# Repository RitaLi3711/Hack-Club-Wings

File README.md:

# Hack-Club-Wings
A passion project for making articulated wings. This is for the frame work. the feathers and decorations will be added afterwords.

Journal Entries 

Inspiration + Frame Decision (Dec 6)

I've always wanted to make a cosplay with wings, as it's a common character trait.
However, the key is that these wings will be articulated. Thus, they'll have to move.

Initially, I wanted to decide whether the wings should have feathers or be like bat wings.
It seems that feathers are more common and the folding will be easier as its individual wings.

Moreover, this is the planning stage as I search for information.

The wings will have to fold.
The way they fold is what differs (point of movement).
From past cosplays, there are 2 main frame types.

3 joints
https://youtu.be/Llf2Xc1FtOM?si=F14uOp8mgtAz-DmK
https://youtu.be/ioxxIeyw33Q?si=4gpekAnZgTFiVE0G

1 joint
https://youtu.be/-S2A7ioRvzg?si=h_PVrSaw3obiIKA0
https://youtube.com/shorts/ro5Fy8bAvns?si=yLVc0ShqFhmZ_Usy
For this project, I will be making wings that move at 1 joint, as that is simpler to build.

Change of Plans (Dec 6)
If I decided to do the 1-point plan, I would need to use at least 2 linear actuators.
I could not find this type of motor option on KaiCad + it is quite pricey (amazon $191 for 1)

Many individuals have done the 3-point method, but mechanically by pulling a piece of string.
To incorporate more circuits into this design, I will be connecting a motor to the pulley. Thus, I can also control when the wings go up and down by controlling how much string the pulley pulls(front, back).
20251206_223540

edit*** wait if the mobile part must be the same for both wings...can't I just use 1 linear actuator?

Created Schematic + Wired the PCB (Dec 6-7)
Ok, so turns out I can't just connect the linear actuator directly to the battery. :(

I'll also be using a fuse, motor controller and microcontroller.
I hope that the fuse and controller will prevent me from catching on fire through overheating. After I add all the feathers and cloth, it'd be a fire hazard, especially under a heavy cosplay costume.

The linear actuator has a DC motor built into it already, so I'll be representing it as a regular DC motor on both the schematic and PCB.
The PCB said that there are 0 errors, so hopefully that's a good sign....

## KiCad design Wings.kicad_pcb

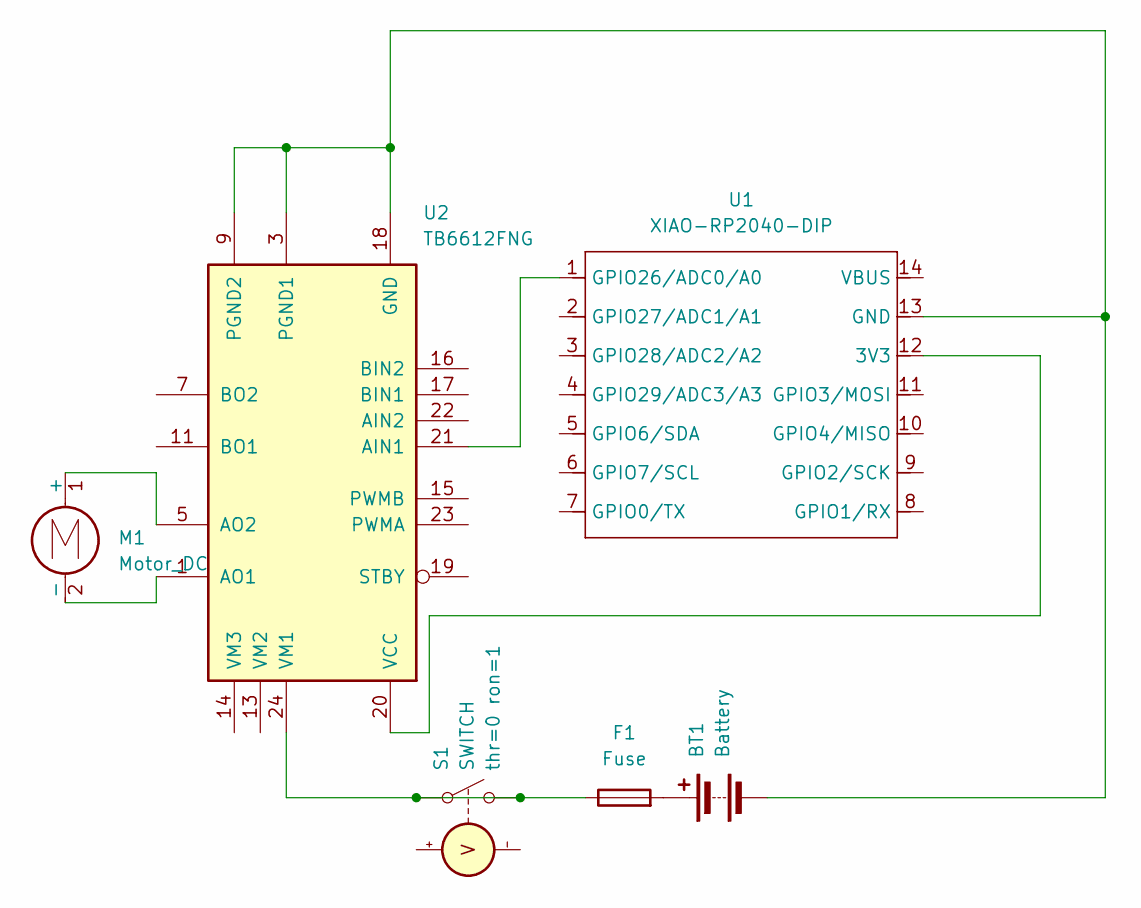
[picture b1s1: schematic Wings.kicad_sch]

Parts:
BT1: Battery; BatteryHolder_Keystone_2479_3xAAA
F1: Fuse; Fuse_1206_3216Metric
M1: Motor_DC; Vybronics_VZ30C1T8219732L
S1: SWITCH; Nidec_Copal_CAS-120A
U1: XIAO-RP2040-DIP
U2: TB6612FNG; SSOP-24_5.3x8.2mm_P0.65mm

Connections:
unnamed: BT1.1 (+), F1.2
unnamed: BT1.2 (-), U1.13 (GND), U2.3 (PGND1), U2.4 (PGND1), U2.9 (PGND2), U2.10 (PGND2), U2.18 (GND)
unnamed: M1.1 (+), U2.5 (AO2), U2.6 (AO2)
unnamed: M1.2 (-), U2.1 (AO1), U2.2 (AO1)
unnamed: F1.1, S1.1 (N+), S1.2 (N-), U2.24 (VM1)
unnamed: U1.12 (3V3), U2.20 (VCC)
unnamed: U1.1 (GPIO26/ADC0/A0), U2.21 (AIN1)
unnamed: U2.11 (BO1), U2.12 (BO1)
unnamed: U2.7 (BO2), U2.8 (BO2)

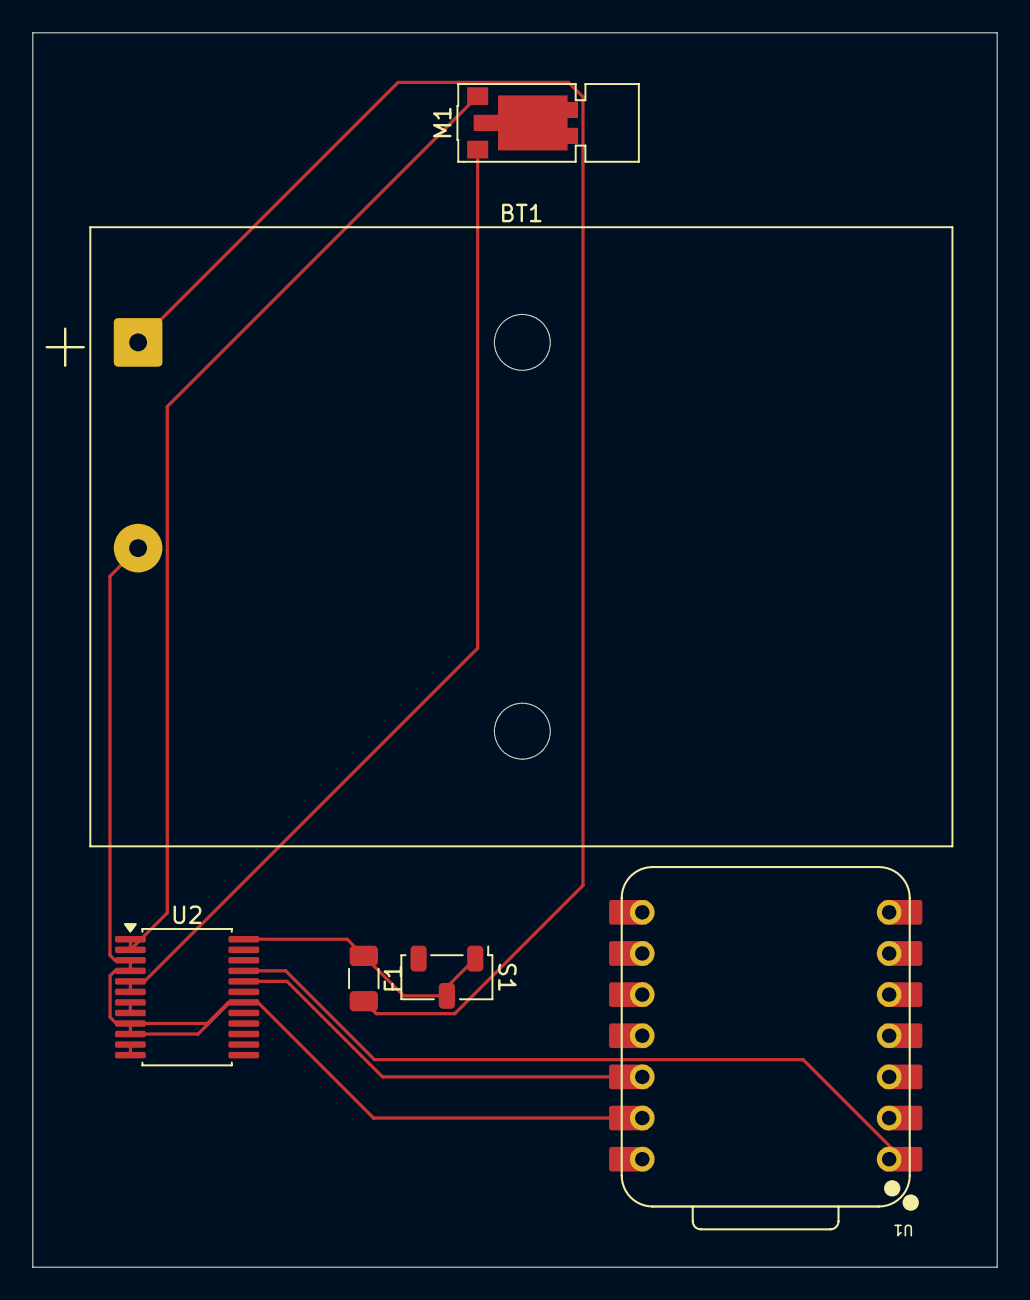
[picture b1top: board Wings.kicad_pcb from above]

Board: 2 copper layers, 59.5 x 76.2 mm, 6 parts (0 on the bottom side), 9 nets.

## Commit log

2025-12-07 Expand README with project inspiration and planning
    Added journal entries detailing inspiration and frame decision for articulated wings project.
